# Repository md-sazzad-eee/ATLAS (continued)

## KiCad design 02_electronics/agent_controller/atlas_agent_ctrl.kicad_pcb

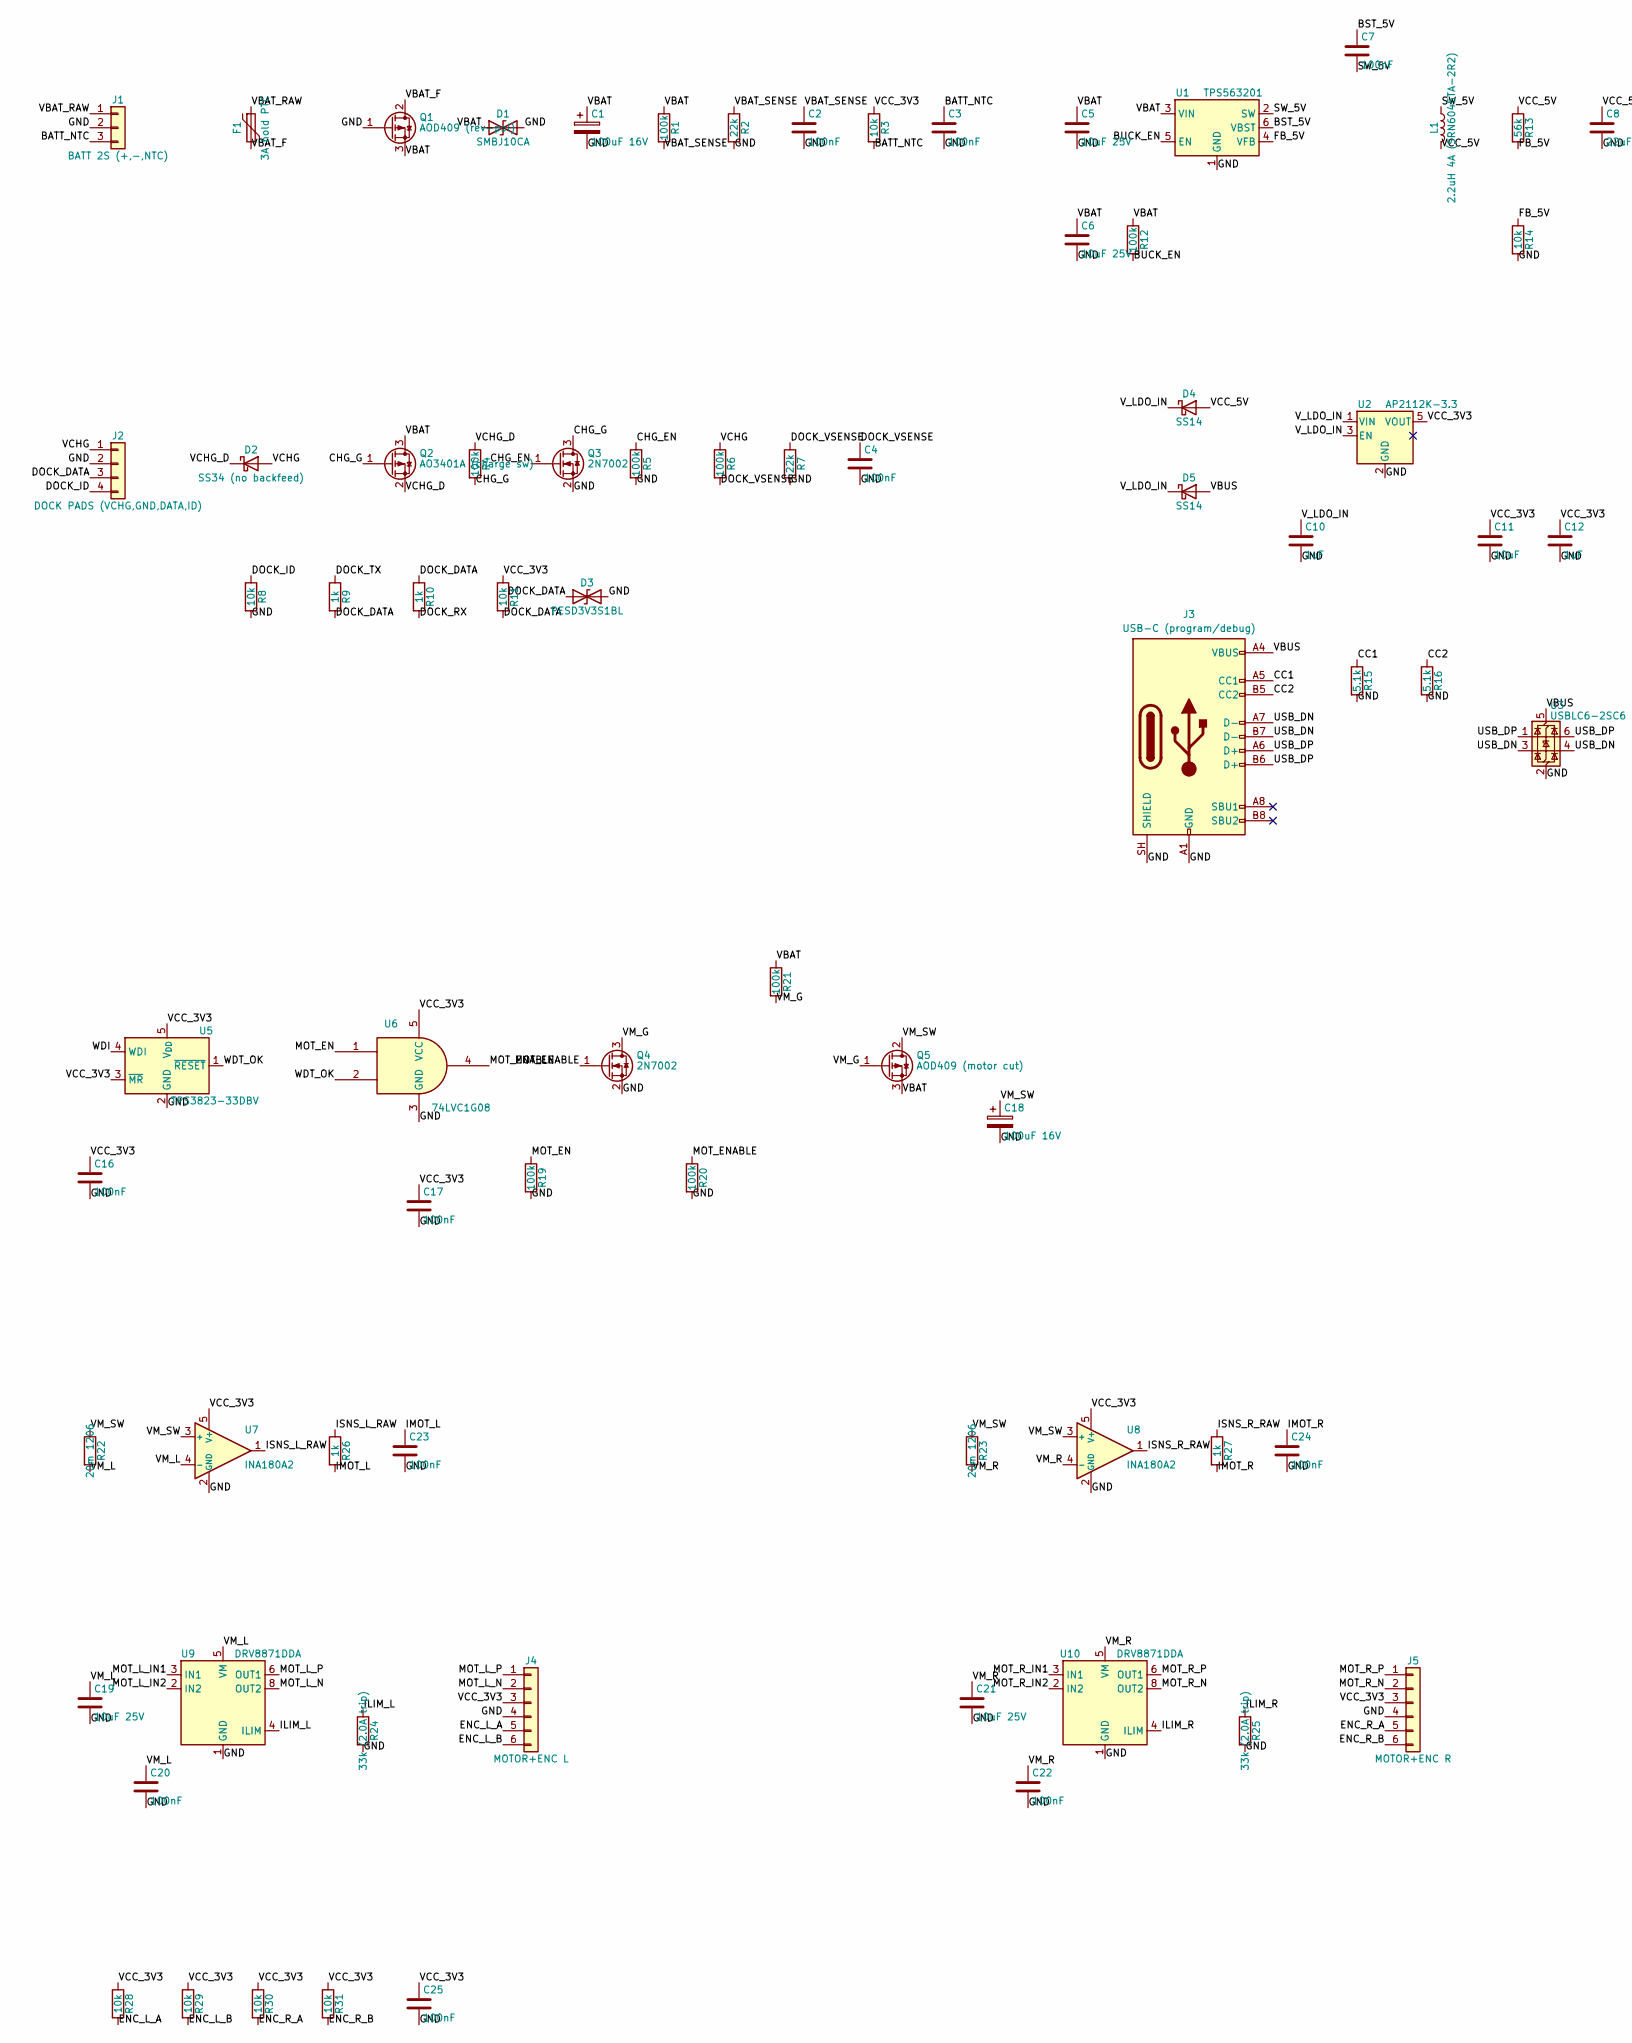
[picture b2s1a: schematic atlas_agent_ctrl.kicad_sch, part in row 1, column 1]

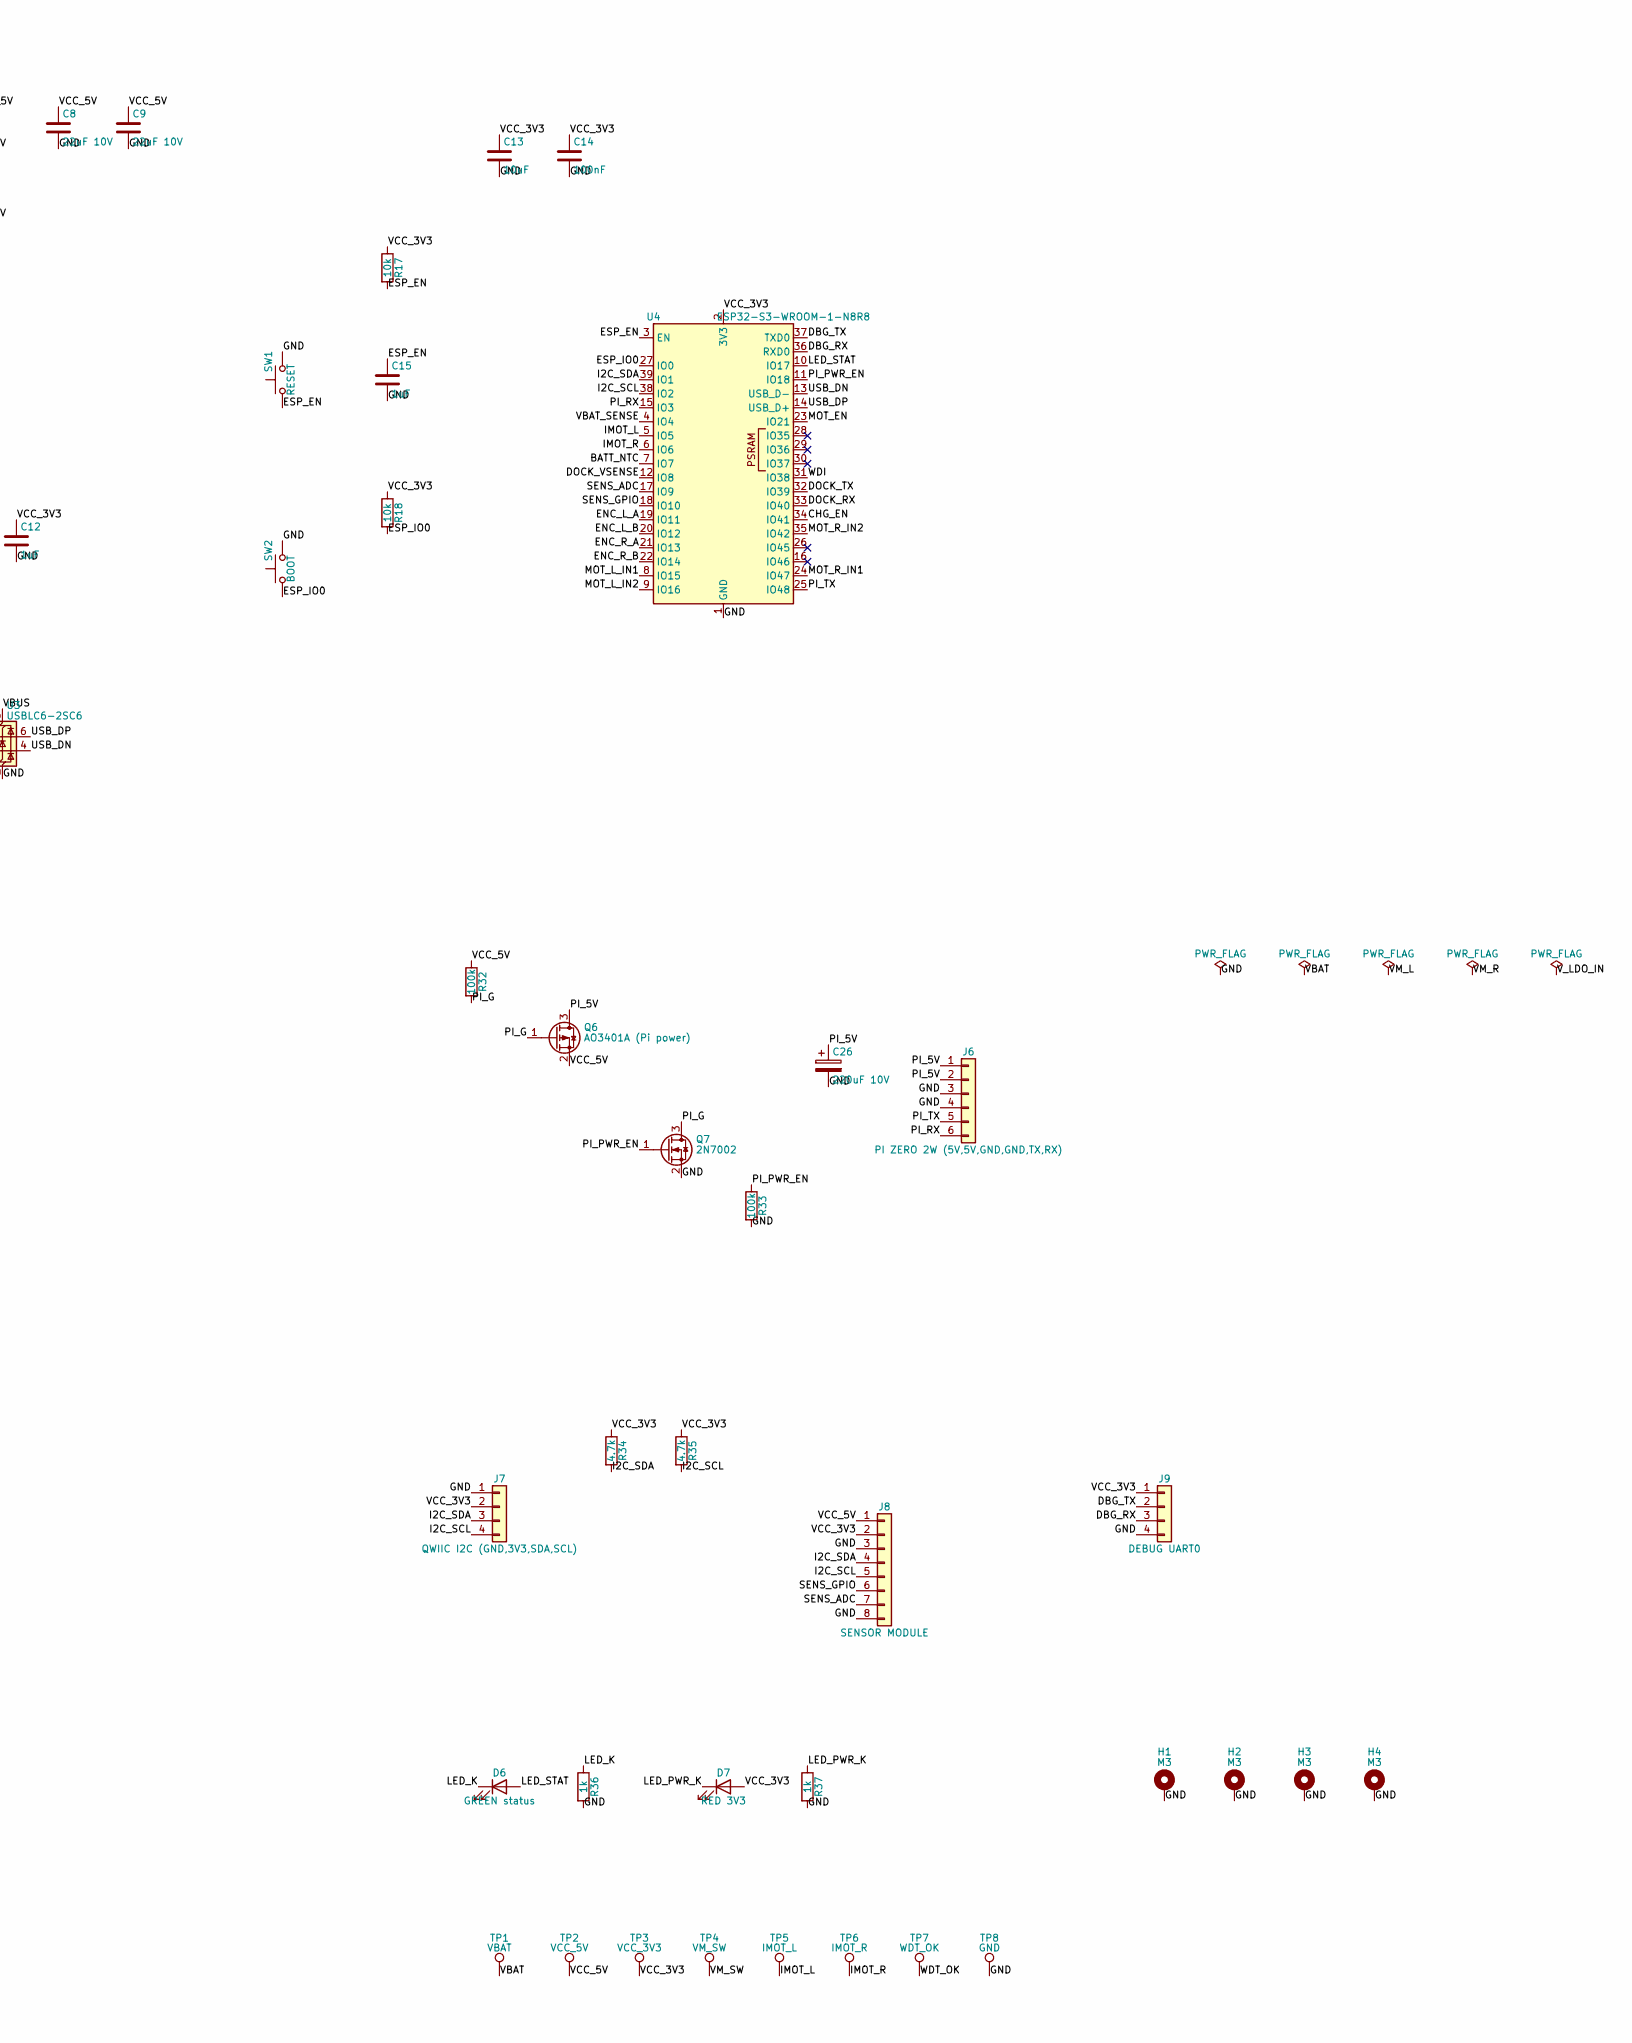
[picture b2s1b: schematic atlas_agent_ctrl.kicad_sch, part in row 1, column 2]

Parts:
C1, C18: 100uF 16V; CP_Elec_6.3x7.7
C2, C3, C4, C7, C14, C16, C17, C20, C22, C23, C24, C25: 100nF; C_0603_1608Metric
C5, C6, C19, C21: 10uF 25V; C_0805_2012Metric
C8, C9: 22uF 10V; C_0805_2012Metric
C10, C12, C15: 1uF; C_0603_1608Metric
C11, C13: 10uF; C_0805_2012Metric
C26: 220uF 10V; CP_Elec_6.3x7.7
D1: SMBJ10CA; D_SMB
D2: SS34 (no backfeed); D_SMA
D3: PESD3V3S1BL; D_SOD-323
D4, D5: SS14; D_SMA
D6: GREEN status; LED_0603_1608Metric
D7: RED 3V3; LED_0603_1608Metric
F1: 3A hold PTC; Fuse_1812_4532Metric
H1, H2, H3, H4: M3; MountingHole_3.2mm_M3_Pad_Via
J1: BATT 2S (+,-,NTC); JST_XH_B3B-XH-A_1x03_P2.50mm_Vertical
J2: DOCK PADS (VCHG,GND,DATA,ID); JST_XH_B4B-XH-A_1x04_P2.50mm_Vertical
J3: USB-C (program/debug); USB_C_Receptacle_GCT_USB4105-xx-A_16P_TopMnt_Horizontal
J4: MOTOR+ENC L; JST_PH_B6B-PH-K_1x06_P2.00mm_Vertical
J5: MOTOR+ENC R; JST_PH_B6B-PH-K_1x06_P2.00mm_Vertical
J6: PI ZERO 2W (5V,5V,GND,GND,TX,RX); JST_GH_SM06B-GHS-TB_1x06-1MP_P1.25mm_Horizontal
J7: QWIIC I2C (GND,3V3,SDA,SCL); JST_SH_SM04B-SRSS-TB_1x04-1MP_P1.00mm_Horizontal
J8: SENSOR MODULE; JST_GH_SM08B-GHS-TB_1x08-1MP_P1.25mm_Horizontal
J9: DEBUG UART0; PinHeader_1x04_P2.54mm_Vertical
L1: 2.2uH 4A (SRN6045TA-2R2); L_Bourns_SRN6045TA
Q1: AOD409 (rev-pol); TO-252-2
Q2: AO3401A (charge sw); SOT-23
Q3, Q4, Q7: 2N7002; SOT-23
Q5: AOD409 (motor cut); TO-252-2
Q6: AO3401A (Pi power); SOT-23
R1, R4, R5, R6, R12, R19, R20, R21, R32, R33: 100k; R_0603_1608Metric
R2, R7: 22k; R_0603_1608Metric
R3, R8, R11, R14, R17, R18, R28, R29, R30, R31: 10k; R_0603_1608Metric
R9, R10, R26, R27, R36, R37: 1k; R_0603_1608Metric
R13: 56k; R_0603_1608Metric
R15, R16: 5.1k; R_0603_1608Metric
R22, R23: 20m 1206; R_1206_3216Metric
R24, R25: 33k (2.0A trip); R_0603_1608Metric
R34, R35: 4.7k; R_0603_1608Metric
SW1: RESET; SW_SPST_TL3342
SW2: BOOT; SW_SPST_TL3342
TP1: VBAT; TestPoint_Pad_D1.5mm
TP2: VCC_5V; TestPoint_Pad_D1.5mm
TP3: VCC_3V3; TestPoint_Pad_D1.5mm
TP4: VM_SW; TestPoint_Pad_D1.5mm
TP5: IMOT_L; TestPoint_Pad_D1.5mm
TP6: IMOT_R; TestPoint_Pad_D1.5mm
TP7: WDT_OK; TestPoint_Pad_D1.5mm
TP8: GND; TestPoint_Pad_D1.5mm
U1: TPS563201; SOT-23-6
U2: AP2112K-3.3; SOT-23-5
U3: USBLC6-2SC6; SOT-23-6
U4: ESP32-S3-WROOM-1-N8R8; ESP32-S3-WROOM-1
U5: TPS3823-33DBV; SOT-23-5
U6: 74LVC1G08; SOT-23-5
U7, U8: INA180A2; SOT-23-5
U9, U10: DRV8871DDA; Texas_HTSOP-8-1EP_3.9x4.9mm_P1.27mm_EP2.95x4.9mm_Mask2.4x3.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

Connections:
/BATT_NTC: C3.1, J1.3, R3.2, U4.7 (IO7)
/BST_5V: C7.1, U1.6 (VBST)
/BUCK_EN: R12.2, U1.5 (EN)
/CC1: J3.A5 (CC1), R15.1
/CC2: J3.B5 (CC2), R16.1
/CHG_EN: Q3.1 (G), R5.1, U4.34 (IO41)
/CHG_G: Q2.1 (G), Q3.3 (D), R4.2
/DBG_RX: J9.3, U4.36 (RXD0)
/DBG_TX: J9.2, U4.37 (TXD0)
/DOCK_DATA: D3.1 (A1), J2.3, R9.2, R10.1, R11.2
/DOCK_ID: J2.4, R8.1
/DOCK_RX: R10.2, U4.33 (IO40)
/DOCK_TX: R9.1, U4.32 (IO39)
/DOCK_VSENSE: C4.1, R6.2, R7.1, U4.12 (IO8)
/ENC_L_A: J4.5, R28.2, U4.19 (IO11)
/ENC_L_B: J4.6, R29.2, U4.20 (IO12)
/ENC_R_A: J5.5, R30.2, U4.21 (IO13)
/ENC_R_B: J5.6, R31.2, U4.22 (IO14)
/ESP_EN: C15.1, R17.2, SW1.1, U4.3 (EN)
/ESP_IO0: R18.2, SW2.1, U4.27 (IO0)
/FB_5V: R13.2, R14.1, U1.4 (VFB)
/GND: C1.2, C2.2, C3.2, C4.2, C5.2, C6.2, C8.2, C9.2, C10.2, C11.2, C12.2, C13.2, C14.2, C15.2, C16.2, C17.2, C18.2, C19.2, C20.2, C21.2, C22.2, C23.2, C24.2, C25.2, C26.2, D1.2 (A2), D3.2 (A2), H1.1, H2.1, H3.1, H4.1, J1.2, J2.2, J3.A1 (GND), J3.A12 (GND), J3.B1 (GND), J3.B12 (GND), J3.SH (SHIELD), J4.4, J5.4, J6.3, J6.4, J7.1, J8.3, J8.8, J9.4, Q1.1 (G), Q3.2 (S), Q4.2 (S), Q7.2 (S), R2.2, R5.2, R7.2, R8.2, R14.2, R15.2, R16.2, R19.2, R20.2, R24.2, R25.2, R33.2, R36.2, R37.2, SW1.2, SW2.2, TP8.1, U1.1 (GND), U2.2 (GND), U3.2 (GND), U4.1 (GND), U4.40 (GND), U4.41 (GND), U5.2 (GND), U6.3 (GND), U7.2 (GND), U8.2 (GND), U9.1 (GND), U9.7 (GND), U9.9 (GND), U10.1 (GND), U10.7 (GND), U10.9 (GND)
/I2C_SCL: J7.4, J8.5, R35.2, U4.38 (IO2)
/I2C_SDA: J7.3, J8.4, R34.2, U4.39 (IO1)
/ILIM_L: R24.1, U9.4 (ILIM)
/ILIM_R: R25.1, U10.4 (ILIM)
/IMOT_L: C23.1, R26.2, TP5.1, U4.5 (IO5)
/IMOT_R: C24.1, R27.2, TP6.1, U4.6 (IO6)
/ISNS_L_RAW: R26.1, U7.1
/ISNS_R_RAW: R27.1, U8.1
/LED_K: D6.1 (K), R36.1
/LED_PWR_K: D7.1 (K), R37.1
/LED_STAT: D6.2 (A), U4.10 (IO17)
/MOT_EN: R19.1, U4.23 (IO21), U6.1
/MOT_ENABLE: Q4.1 (G), R20.1, U6.4
/MOT_L_IN1: U4.8 (IO15), U9.3 (IN1)
/MOT_L_IN2: U4.9 (IO16), U9.2 (IN2)
/MOT_L_N: J4.2, U9.8 (OUT2)
/MOT_L_P: J4.1, U9.6 (OUT1)
/MOT_R_IN1: U4.24 (IO47), U10.3 (IN1)
/MOT_R_IN2: U4.35 (IO42), U10.2 (IN2)
/MOT_R_N: J5.2, U10.8 (OUT2)
/MOT_R_P: J5.1, U10.6 (OUT1)
/PI_5V: C26.1, J6.1, J6.2, Q6.3 (D)
/PI_G: Q6.1 (G), Q7.3 (D), R32.2
/PI_PWR_EN: Q7.1 (G), R33.1, U4.11 (IO18)
/PI_RX: J6.6, U4.15 (IO3)
/PI_TX: J6.5, U4.25 (IO48)
/SENS_ADC: J8.7, U4.17 (IO9)
/SENS_GPIO: J8.6, U4.18 (IO10)
/SW_5V: C7.2, L1.1, U1.2 (SW)
/USB_DN: J3.A7 (D-), J3.B7 (D-), U3.3 (I/O2), U3.4 (I/O2), U4.13 (USB_D-)
/USB_DP: J3.A6 (D+), J3.B6 (D+), U3.1 (I/O1), U3.6 (I/O1), U4.14 (USB_D+)
/VBAT: C1.1, C5.1, C6.1, D1.1 (A1), Q1.3 (S), Q2.3 (D), Q5.3 (S), R1.1, R12.1, R21.1, TP1.1, U1.3 (VIN)
/VBAT_F: F1.2, Q1.2 (D)
/VBAT_RAW: F1.1, J1.1
/VBAT_SENSE: C2.1, R1.2, R2.1, U4.4 (IO4)
/VBUS: D5.2 (A), J3.A4 (VBUS), J3.A9 (VBUS), J3.B4 (VBUS), J3.B9 (VBUS), U3.5 (VBUS)
/VCC_3V3: C11.1, C12.1, C13.1, C14.1, C16.1, C17.1, C25.1, D7.2 (A), J4.3, J5.3, J7.2, J8.2, J9.1, R3.1, R11.1, R17.1, R18.1, R28.1, R29.1, R30.1, R31.1, R34.1, R35.1, TP3.1, U2.5 (VOUT), U4.2 (3V3), U5.3 (~MR), U5.5 (V_{DD}), U6.5 (VCC), U7.5 (V+), U8.5 (V+)
/VCC_5V: C8.1, C9.1, D4.2 (A), J8.1, L1.2, Q6.2 (S), R13.1, R32.1, TP2.1
/VCHG: D2.2 (A), J2.1, R6.1
/VCHG_D: D2.1 (K), Q2.2 (S), R4.1
/VM_G: Q4.3 (D), Q5.1 (G), R21.2
/VM_L: C19.1, C20.1, R22.2, U7.4 (-), U9.5 (VM)
/VM_R: C21.1, C22.1, R23.2, U8.4 (-), U10.5 (VM)
/VM_SW: C18.1, Q5.2 (D), R22.1, R23.1, TP4.1, U7.3 (+), U8.3 (+)
/V_LDO_IN: C10.1, D4.1 (K), D5.1 (K), U2.1 (VIN), U2.3 (EN)
/WDI: U4.31 (IO38), U5.4 (WDI)
/WDT_OK: TP7.1, U5.1 (~RESET), U6.2

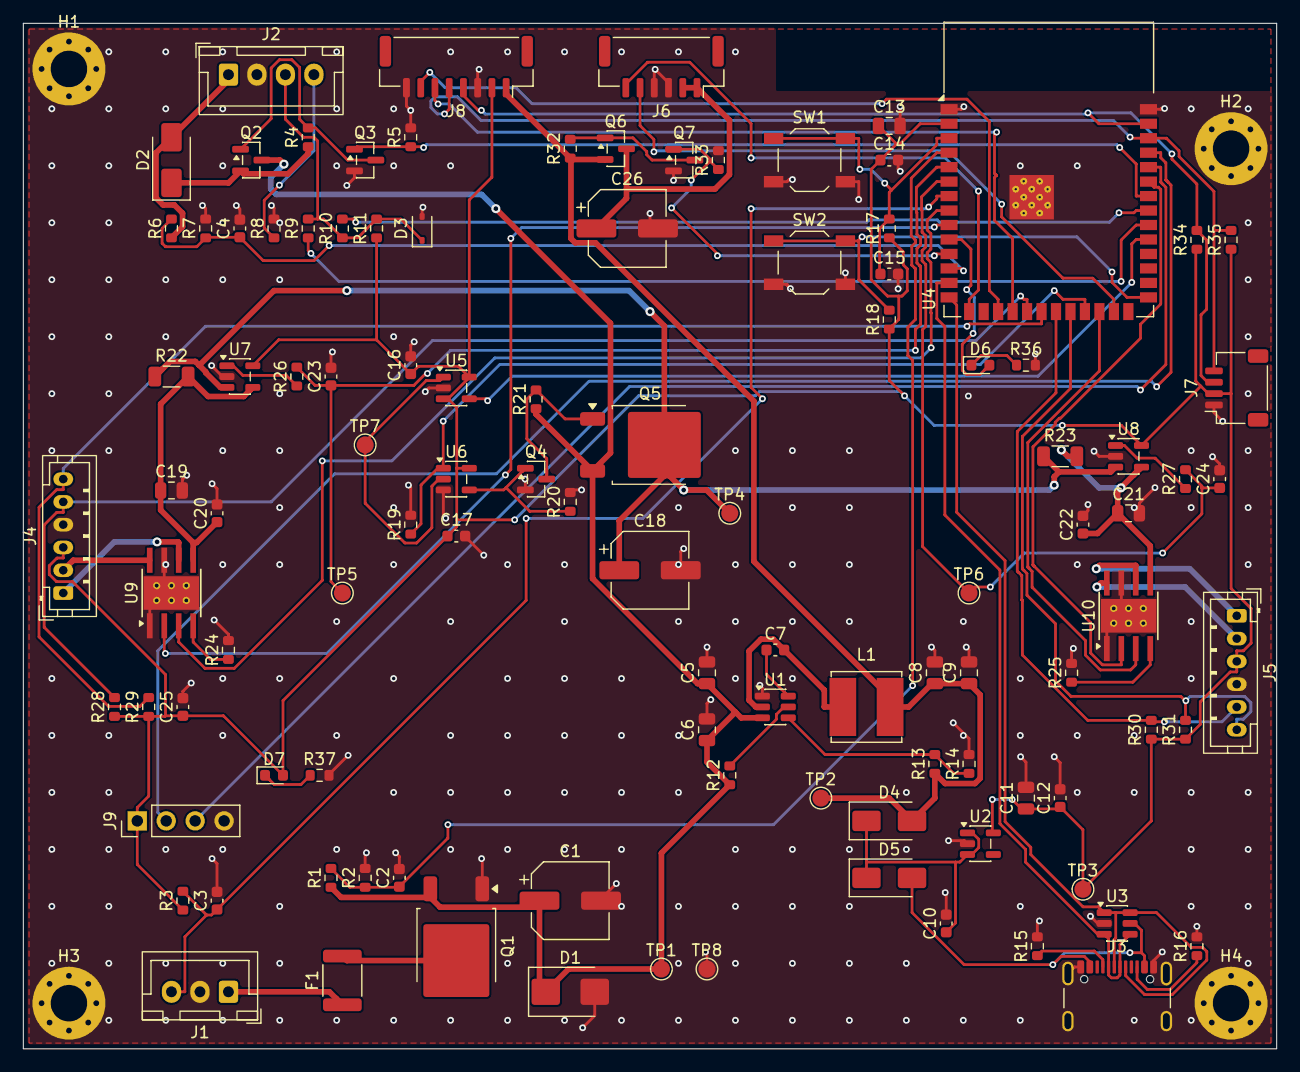
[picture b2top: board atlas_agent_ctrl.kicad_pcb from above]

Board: 2 copper layers, 110.0 x 90.0 mm, 112 parts (0 on the bottom side), 69 nets.

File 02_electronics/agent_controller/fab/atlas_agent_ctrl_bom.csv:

"Refs","Value","Footprint","Qty","DNP"
"C1","100uF 16V","Capacitor_SMD:CP_Elec_6.3x7.7","1",""
"C2","100nF","Capacitor_SMD:C_0603_1608Metric","1",""
"C3","100nF","Capacitor_SMD:C_0603_1608Metric","1",""
"C4","100nF","Capacitor_SMD:C_0603_1608Metric","1",""
"C5","10uF 25V","Capacitor_SMD:C_0805_2012Metric","1",""
"C6","10uF 25V","Capacitor_SMD:C_0805_2012Metric","1",""
"C7","100nF","Capacitor_SMD:C_0603_1608Metric","1",""
"C8","22uF 10V","Capacitor_SMD:C_0805_2012Metric","1",""
"C9","22uF 10V","Capacitor_SMD:C_0805_2012Metric","1",""
"C10","1uF","Capacitor_SMD:C_0603_1608Metric","1",""
"C11","10uF","Capacitor_SMD:C_0805_2012Metric","1",""
"C12","1uF","Capacitor_SMD:C_0603_1608Metric","1",""
"C13","10uF","Capacitor_SMD:C_0805_2012Metric","1",""
"C14","100nF","Capacitor_SMD:C_0603_1608Metric","1",""
"C15","1uF","Capacitor_SMD:C_0603_1608Metric","1",""
"C16","100nF","Capacitor_SMD:C_0603_1608Metric","1",""
"C17","100nF","Capacitor_SMD:C_0603_1608Metric","1",""
"C18","100uF 16V","Capacitor_SMD:CP_Elec_6.3x7.7","1",""
"C19","10uF 25V","Capacitor_SMD:C_0805_2012Metric","1",""
"C20","100nF","Capacitor_SMD:C_0603_1608Metric","1",""
"C21","10uF 25V","Capacitor_SMD:C_0805_2012Metric","1",""
"C22","100nF","Capacitor_SMD:C_0603_1608Metric","1",""
"C23","100nF","Capacitor_SMD:C_0603_1608Metric","1",""
"C24","100nF","Capacitor_SMD:C_0603_1608Metric","1",""
"C25","100nF","Capacitor_SMD:C_0603_1608Metric","1",""
"C26","220uF 10V","Capacitor_SMD:CP_Elec_6.3x7.7","1",""
"D1","SMBJ10CA","Diode_SMD:D_SMB","1",""
"D2","SS34 (no backfeed)","Diode_SMD:D_SMA","1",""
"D3","PESD3V3S1BL","Diode_SMD:D_SOD-323","1",""
"D4","SS14","Diode_SMD:D_SMA","1",""
"D5","SS14","Diode_SMD:D_SMA","1",""
"D6","GREEN status","LED_SMD:LED_0603_1608Metric","1",""
"D7","RED 3V3","LED_SMD:LED_0603_1608Metric","1",""
"F1","3A hold PTC","Fuse:Fuse_1812_4532Metric","1",""
"H1","M3","MountingHole:MountingHole_3.2mm_M3_Pad_Via","1",""
"H2","M3","MountingHole:MountingHole_3.2mm_M3_Pad_Via","1",""
"H3","M3","MountingHole:MountingHole_3.2mm_M3_Pad_Via","1",""
"H4","M3","MountingHole:MountingHole_3.2mm_M3_Pad_Via","1",""
"J1","BATT 2S (+,-,NTC)","Connector_JST:JST_XH_B3B-XH-A_1x03_P2.50mm_Vertical","1",""
"J2","DOCK PADS (VCHG,GND,DATA,ID)","Connector_JST:JST_XH_B4B-XH-A_1x04_P2.50mm_Vertical","1",""
"J3","USB-C (program/debug)","Connector_USB:USB_C_Receptacle_GCT_USB4105-xx-A_16P_TopMnt_Horizontal","1",""
"J4","MOTOR+ENC L","Connector_JST:JST_PH_B6B-PH-K_1x06_P2.00mm_Vertical","1",""
"J5","MOTOR+ENC R","Connector_JST:JST_PH_B6B-PH-K_1x06_P2.00mm_Vertical","1",""
"J6","PI ZERO 2W (5V,5V,GND,GND,TX,RX)","Connector_JST:JST_GH_SM06B-GHS-TB_1x06-1MP_P1.25mm_Horizontal","1",""
"J7","QWIIC I2C (GND,3V3,SDA,SCL)","Connector_JST:JST_SH_SM04B-SRSS-TB_1x04-1MP_P1.00mm_Horizontal","1",""
"J8","SENSOR MODULE","Connector_JST:JST_GH_SM08B-GHS-TB_1x08-1MP_P1.25mm_Horizontal","1",""
"J9","DEBUG UART0","Connector_PinHeader_2.54mm:PinHeader_1x04_P2.54mm_Vertical","1",""
"L1","2.2uH 4A (SRN6045TA-2R2)","Inductor_SMD:L_Bourns_SRN6045TA","1",""
"Q1","AOD409 (rev-pol)","Package_TO_SOT_SMD:TO-252-2","1",""
"Q2","AO3401A (charge sw)","Package_TO_SOT_SMD:SOT-23","1",""
"Q3","2N7002","Package_TO_SOT_SMD:SOT-23","1",""
"Q4","2N7002","Package_TO_SOT_SMD:SOT-23","1",""
"Q5","AOD409 (motor cut)","Package_TO_SOT_SMD:TO-252-2","1",""
"Q6","AO3401A (Pi power)","Package_TO_SOT_SMD:SOT-23","1",""
"Q7","2N7002","Package_TO_SOT_SMD:SOT-23","1",""
"R1","100k","Resistor_SMD:R_0603_1608Metric","1",""
"R2","22k","Resistor_SMD:R_0603_1608Metric","1",""
"R3","10k","Resistor_SMD:R_0603_1608Metric","1",""
"R4","100k","Resistor_SMD:R_0603_1608Metric","1",""
"R5","100k","Resistor_SMD:R_0603_1608Metric","1",""
"R6","100k","Resistor_SMD:R_0603_1608Metric","1",""
"R7","22k","Resistor_SMD:R_0603_1608Metric","1",""
"R8","10k","Resistor_SMD:R_0603_1608Metric","1",""
"R9","1k","Resistor_SMD:R_0603_1608Metric","1",""
"R10","1k","Resistor_SMD:R_0603_1608Metric","1",""
"R11","10k","Resistor_SMD:R_0603_1608Metric","1",""
"R12","100k","Resistor_SMD:R_0603_1608Metric","1",""
"R13","56k","Resistor_SMD:R_0603_1608Metric","1",""
"R14","10k","Resistor_SMD:R_0603_1608Metric","1",""
"R15","5.1k","Resistor_SMD:R_0603_1608Metric","1",""
"R16","5.1k","Resistor_SMD:R_0603_1608Metric","1",""
"R17","10k","Resistor_SMD:R_0603_1608Metric","1",""
"R18","10k","Resistor_SMD:R_0603_1608Metric","1",""
"R19","100k","Resistor_SMD:R_0603_1608Metric","1",""
"R20","100k","Resistor_SMD:R_0603_1608Metric","1",""
"R21","100k","Resistor_SMD:R_0603_1608Metric","1",""
"R22","20m 1206","Resistor_SMD:R_1206_3216Metric","1",""
"R23","20m 1206","Resistor_SMD:R_1206_3216Metric","1",""
"R24","33k (2.0A trip)","Resistor_SMD:R_0603_1608Metric","1",""
"R25","33k (2.0A trip)","Resistor_SMD:R_0603_1608Metric","1",""
"R26","1k","Resistor_SMD:R_0603_1608Metric","1",""
"R27","1k","Resistor_SMD:R_0603_1608Metric","1",""
"R28","10k","Resistor_SMD:R_0603_1608Metric","1",""
"R29","10k","Resistor_SMD:R_0603_1608Metric","1",""
"R30","10k","Resistor_SMD:R_0603_1608Metric","1",""
"R31","10k","Resistor_SMD:R_0603_1608Metric","1",""
"R32","100k","Resistor_SMD:R_0603_1608Metric","1",""
"R33","100k","Resistor_SMD:R_0603_1608Metric","1",""
"R34","4.7k","Resistor_SMD:R_0603_1608Metric","1",""
"R35","4.7k","Resistor_SMD:R_0603_1608Metric","1",""
"R36","1k","Resistor_SMD:R_0603_1608Metric","1",""
"R37","1k","Resistor_SMD:R_0603_1608Metric","1",""
"SW1","RESET","Button_Switch_SMD:SW_SPST_TL3342","1",""
"SW2","BOOT","Button_Switch_SMD:SW_SPST_TL3342","1",""
"TP1","VBAT","TestPoint:TestPoint_Pad_D1.5mm","1",""
"TP2","VCC_5V","TestPoint:TestPoint_Pad_D1.5mm","1",""
"TP3","VCC_3V3","TestPoint:TestPoint_Pad_D1.5mm","1",""
"TP4","VM_SW","TestPoint:TestPoint_Pad_D1.5mm","1",""
"TP5","IMOT_L","TestPoint:TestPoint_Pad_D1.5mm","1",""
"TP6","IMOT_R","TestPoint:TestPoint_Pad_D1.5mm","1",""
"TP7","WDT_OK","TestPoint:TestPoint_Pad_D1.5mm","1",""
"TP8","GND","TestPoint:TestPoint_Pad_D1.5mm","1",""
"U1","TPS563201","Package_TO_SOT_SMD:SOT-23-6","1",""
"U2","AP2112K-3.3","Package_TO_SOT_SMD:SOT-23-5","1",""
"U3","USBLC6-2SC6","Package_TO_SOT_SMD:SOT-23-6","1",""
"U4","ESP32-S3-WROOM-1-N8R8","RF_Module:ESP32-S3-WROOM-1","1",""
"U5","TPS3823-33DBV","Package_TO_SOT_SMD:SOT-23-5","1",""
"U6","74LVC1G08","Package_TO_SOT_SMD:SOT-23-5","1",""
"U7","INA180A2","Package_TO_SOT_SMD:SOT-23-5","1",""
"U8","INA180A2","Package_TO_SOT_SMD:SOT-23-5","1",""
"U9","DRV8871DDA","Package_SO:Texas_HTSOP-8-1EP_3.9x4.9mm_P1.27mm_EP2.95x4.9mm_Mask2.4x3.1mm_ThermalVias","1",""
"U10","DRV8871DDA","Package_SO:Texas_HTSOP-8-1EP_3.9x4.9mm_P1.27mm_EP2.95x4.9mm_Mask2.4x3.1mm_ThermalVias","1",""

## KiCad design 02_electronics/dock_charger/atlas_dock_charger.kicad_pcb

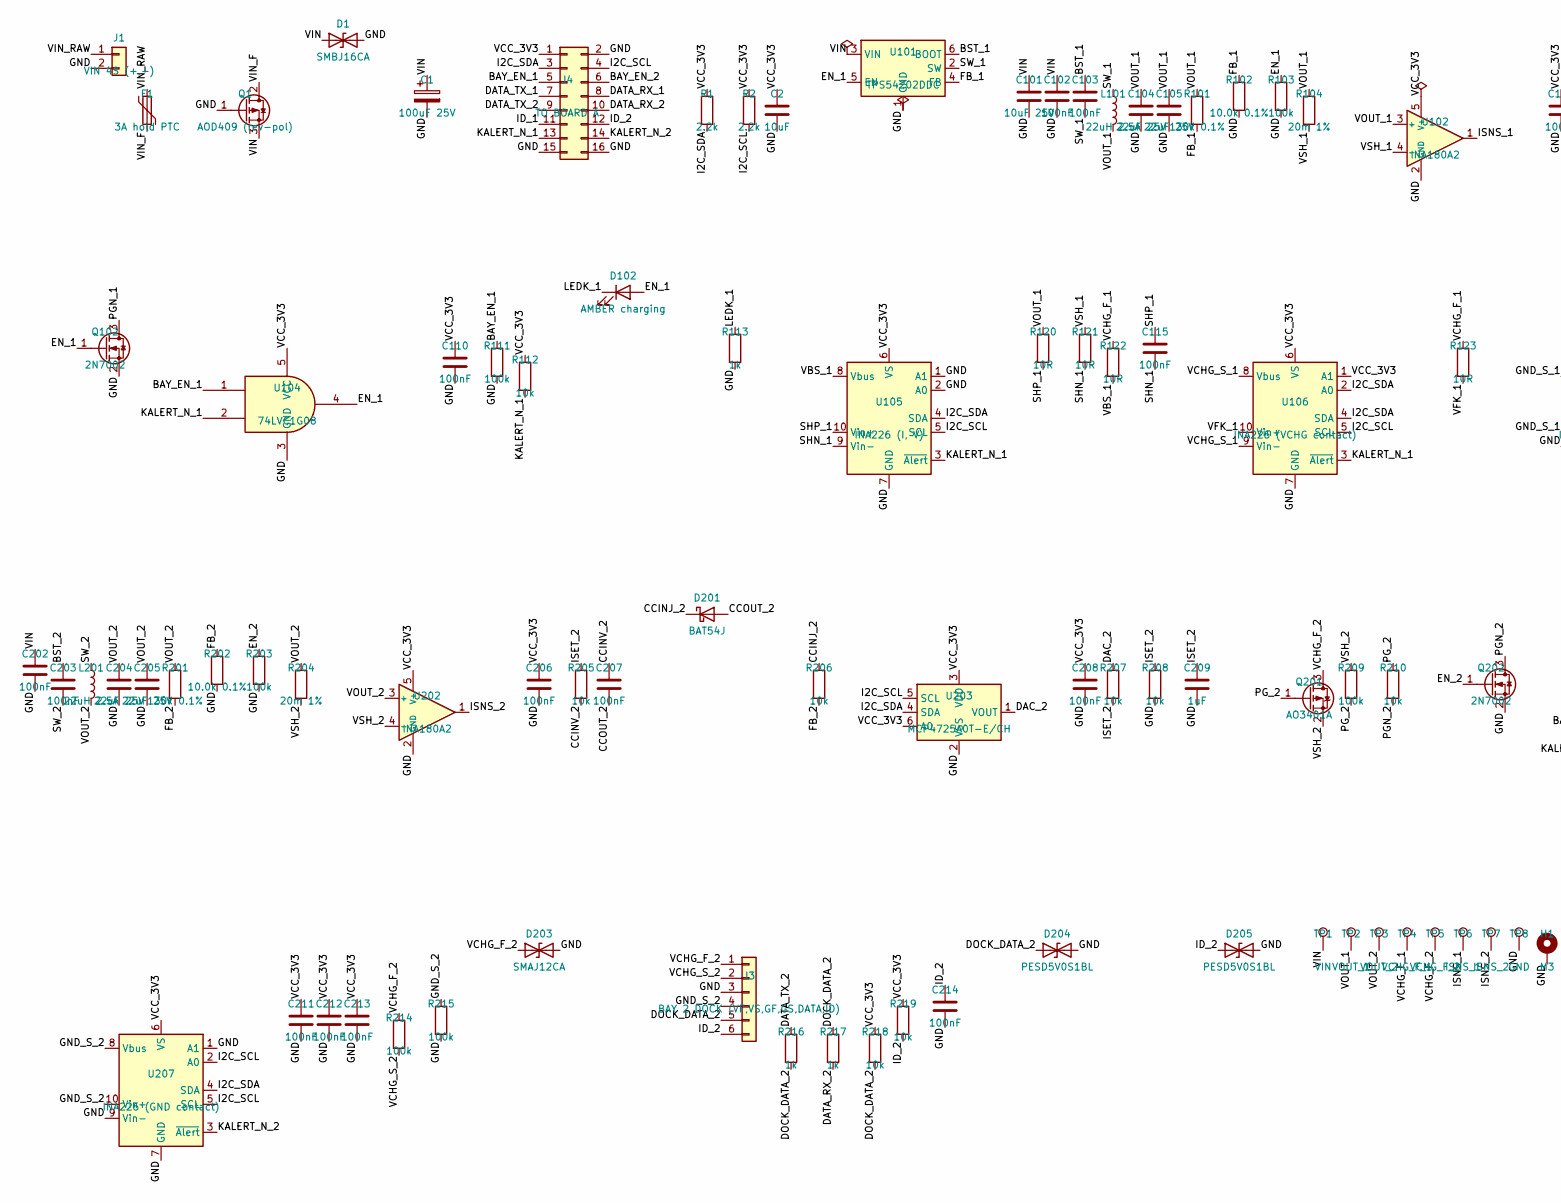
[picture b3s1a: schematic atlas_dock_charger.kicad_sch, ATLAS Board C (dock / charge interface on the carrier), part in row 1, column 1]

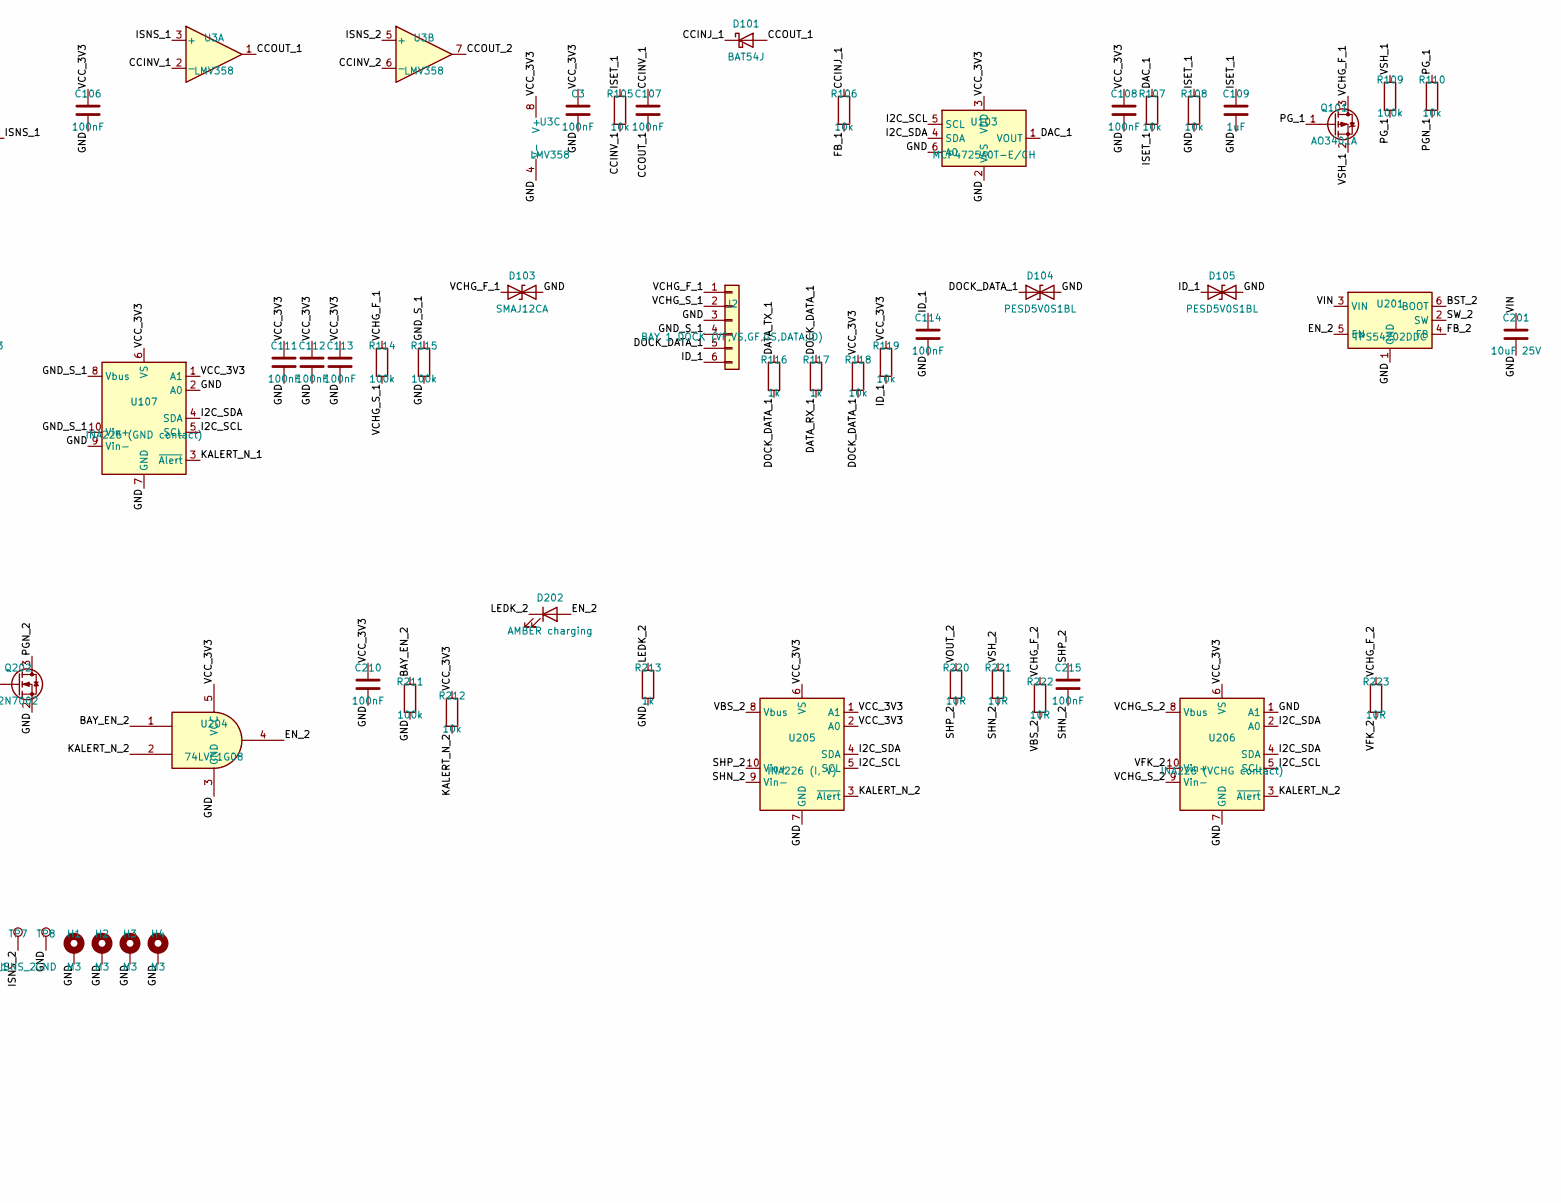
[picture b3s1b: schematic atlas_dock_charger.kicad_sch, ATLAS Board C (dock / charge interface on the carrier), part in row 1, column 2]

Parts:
C1: 100uF 25V; CP_Elec_8x10
C2: 10uF; C_0805_2012Metric
C3, C102, C103, C106, C107, C108, C110, C111, C112, C113, C114, C115, C202, C203, C206, C207, C208, C210, C211, C212, C213, C214, C215: 100nF; C_0603_1608Metric
C101, C201: 10uF 25V; C_1206_3216Metric
C104, C105, C204, C205: 22uF 25V; C_1206_3216Metric
C109, C209: 1uF; C_0603_1608Metric
D1: SMBJ16CA; D_SMB
D101, D201: BAT54J; D_SOD-323
D102, D202: AMBER charging; LED_0603_1608Metric
D103, D203: SMAJ12CA; D_SMA
D104, D105, D204, D205: PESD5V0S1BL; D_SOD-323
F1: 3A hold PTC; Fuse_1812_4532Metric
H1, H2, H3, H4: M3; MountingHole_3.2mm_M3_Pad_Via
J1: VIN 4S (+,-); AMASS_XT30PW-M_1x02_P2.50mm_Horizontal
J2: BAY 1 DOCK (VF,VS,GF,GS,DATA,ID); JST_XH_B6B-XH-A_1x06_P2.50mm_Vertical
J3: BAY 2 DOCK (VF,VS,GF,GS,DATA,ID); JST_XH_B6B-XH-A_1x06_P2.50mm_Vertical
J4: TO BOARD A; PinHeader_2x08_P2.54mm_Vertical
L101, L201: 22uH 2.5A; L_Bourns_SRR1260
Q1: AOD409 (rev-pol); TO-252-2
Q101, Q201: AO3401A; SOT-23
Q102, Q202: 2N7002; SOT-23
R1, R2: 2.2k; R_0603_1608Metric
R101, R201: 130k 0.1%; R_0603_1608Metric
R102, R202: 10.0k 0.1%; R_0603_1608Metric
R103, R109, R111, R114, R115, R203, R209, R211, R214, R215: 100k; R_0603_1608Metric
R104, R204: 20m 1%; R_1206_3216Metric
R105, R106, R107, R108, R110, R112, R118, R119, R205, R206, R207, R208, R210, R212, R218, R219: 10k; R_0603_1608Metric
R113, R116, R117, R213, R216, R217: 1k; R_0603_1608Metric
R120, R121, R122, R123, R220, R221, R222, R223: 10R; R_0603_1608Metric
TP1: VIN; TestPoint_Pad_D1.5mm
TP2: VOUT_1; TestPoint_Pad_D1.5mm
TP3: VOUT_2; TestPoint_Pad_D1.5mm
TP4: VCHG_F_1; TestPoint_Pad_D1.5mm
TP5: VCHG_F_2; TestPoint_Pad_D1.5mm
TP6: ISNS_1; TestPoint_Pad_D1.5mm
TP7: ISNS_2; TestPoint_Pad_D1.5mm
TP8: GND; TestPoint_Pad_D1.5mm
U3: LMV358; SOIC-8_3.9x4.9mm_P1.27mm
U101, U201: TPS54202DDC; SOT-23-6
U102, U202: INA180A2; SOT-23-5
U103, U203: MCP4725A0T-E/CH; SOT-23-6
U104, U204: 74LVC1G08; SOT-23-5
U105, U205: INA226 (I, V); MSOP-10_3x3mm_P0.5mm
U106, U206: INA226 (VCHG contact); MSOP-10_3x3mm_P0.5mm
U107, U207: INA226 (GND contact); MSOP-10_3x3mm_P0.5mm

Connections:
/BAY_EN_1: J4.5, R111.1, U104.1
/BAY_EN_2: J4.6, R211.1, U204.1
/BST_1: C103.1, U101.6 (BOOT)
/BST_2: C203.1, U201.6 (BOOT)
/CCINJ_1: D101.1 (K), R106.1
/CCINJ_2: D201.1 (K), R206.1
/CCINV_1: C107.1, R105.2, U3.2 (-)
/CCINV_2: C207.1, R205.2, U3.6 (-)
/CCOUT_1: C107.2, D101.2 (A), U3.1
/CCOUT_2: C207.2, D201.2 (A), U3.7
/DAC_1: R107.1, U103.1 (VOUT)
/DAC_2: R207.1, U203.1 (VOUT)
/DATA_RX_1: J4.8, R117.2
/DATA_RX_2: J4.10, R217.2
/DATA_TX_1: J4.7, R116.1
/DATA_TX_2: J4.9, R216.1
/DOCK_DATA_1: D104.1 (A1), J2.5, R116.2, R117.1, R118.2
/DOCK_DATA_2: D204.1 (A1), J3.5, R216.2, R217.1, R218.2
/EN_1: D102.2 (A), Q102.1 (G), R103.1, U101.5 (EN), U104.4
/EN_2: D202.2 (A), Q202.1 (G), R203.1, U201.5 (EN), U204.4
/FB_1: R101.2, R102.1, R106.2, U101.4 (FB)
/FB_2: R201.2, R202.1, R206.2, U201.4 (FB)
/GND: C1.2, C2.2, C3.2, C101.2, C102.2, C104.2, C105.2, C106.2, C108.2, C109.2, C110.2, C111.2, C112.2, C113.2, C114.2, C201.2, C202.2, C204.2, C205.2, C206.2, C208.2, C209.2, C210.2, C211.2, C212.2, C213.2, C214.2, D1.2 (A2), D103.2 (A2), D104.2 (A2), D105.2 (A2), D203.2 (A2), D204.2 (A2), D205.2 (A2), H1.1, H2.1, H3.1, H4.1, J1.2, J2.3, J3.3, J4.2, J4.15, J4.16, Q1.1 (G), Q102.2 (S), Q202.2 (S), R102.2, R103.2, R108.2, R111.2, R113.2, R115.2, R202.2, R203.2, R208.2, R211.2, R213.2, R215.2, TP8.1, U3.4 (V-), U101.1 (GND), U102.2 (GND), U103.2 (VSS), U103.6 (A0), U104.3 (GND), U105.1 (A1), U105.2 (A0), U105.7 (GND), U106.7 (GND), U107.2 (A0), U107.7 (GND), U107.9 (Vin-), U201.1 (GND), U202.2 (GND), U203.2 (VSS), U204.3 (GND), U205.7 (GND), U206.1 (A1), U206.7 (GND), U207.1 (A1), U207.7 (GND), U207.9 (Vin-)
/GND_S_1: J2.4, R115.1, U107.8 (Vbus), U107.10 (Vin+)
/GND_S_2: J3.4, R215.1, U207.8 (Vbus), U207.10 (Vin+)
/I2C_SCL: J4.4, R2.2, U103.5 (SCL), U105.5 (SCL), U106.5 (SCL), U107.5 (SCL), U203.5 (SCL), U205.5 (SCL), U206.5 (SCL), U207.2 (A0), U207.5 (SCL)
/I2C_SDA: J4.3, R1.2, U103.4 (SDA), U105.4 (SDA), U106.2 (A0), U106.4 (SDA), U107.4 (SDA), U203.4 (SDA), U205.4 (SDA), U206.2 (A0), U206.4 (SDA), U207.4 (SDA)
/ID_1: C114.1, D105.1 (A1), J2.6, J4.11, R119.2
/ID_2: C214.1, D205.1 (A1), J3.6, J4.12, R219.2
/ISET_1: C109.1, R105.1, R107.2, R108.1
/ISET_2: C209.1, R205.1, R207.2, R208.1
/ISNS_1: TP6.1, U3.3 (+), U102.1
/ISNS_2: TP7.1, U3.5 (+), U202.1
/KALERT_N_1: J4.13, R112.2, U104.2, U105.3 (~Alert), U106.3 (~Alert), U107.3 (~Alert)
/KALERT_N_2: J4.14, R212.2, U204.2, U205.3 (~Alert), U206.3 (~Alert), U207.3 (~Alert)
/LEDK_1: D102.1 (K), R113.1
/LEDK_2: D202.1 (K), R213.1
/PGN_1: Q102.3 (D), R110.2
/PGN_2: Q202.3 (D), R210.2
/PG_1: Q101.1 (G), R109.2, R110.1
/PG_2: Q201.1 (G), R209.2, R210.1
/SHN_1: C115.2, R121.2, U105.9 (Vin-)
/SHN_2: C215.2, R221.2, U205.9 (Vin-)
/SHP_1: C115.1, R120.2, U105.10 (Vin+)
/SHP_2: C215.1, R220.2, U205.10 (Vin+)
/SW_1: C103.2, L101.1, U101.2 (SW)
/SW_2: C203.2, L201.1, U201.2 (SW)
/VBS_1: R122.2, U105.8 (Vbus)
/VBS_2: R222.2, U205.8 (Vbus)
/VCC_3V3: C2.1, C3.1, C106.1, C108.1, C110.1, C111.1, C112.1, C113.1, C206.1, C208.1, C210.1, C211.1, C212.1, C213.1, J4.1, R1.1, R2.1, R112.1, R118.1, R119.1, R212.1, R218.1, R219.1, U3.8 (V+), U102.5 (V+), U103.3 (VDD), U104.5 (VCC), U105.6 (VS), U106.1 (A1), U106.6 (VS), U107.1 (A1), U107.6 (VS), U202.5 (V+), U203.3 (VDD), U203.6 (A0), U204.5 (VCC), U205.1 (A1), U205.2 (A0), U205.6 (VS), U206.6 (VS), U207.6 (VS)
/VCHG_F_1: D103.1 (A1), J2.1, Q101.3 (D), R114.1, R122.1, R123.1, TP4.1
/VCHG_F_2: D203.1 (A1), J3.1, Q201.3 (D), R214.1, R222.1, R223.1, TP5.1
/VCHG_S_1: J2.2, R114.2, U106.8 (Vbus), U106.9 (Vin-)
/VCHG_S_2: J3.2, R214.2, U206.8 (Vbus), U206.9 (Vin-)
/VFK_1: R123.2, U106.10 (Vin+)
/VFK_2: R223.2, U206.10 (Vin+)
/VIN: C1.1, C101.1, C102.1, C201.1, C202.1, D1.1 (A1), Q1.3 (S), TP1.1, U101.3 (VIN), U201.3 (VIN)
/VIN_F: F1.2, Q1.2 (D)
/VIN_RAW: F1.1, J1.1
/VOUT_1: C104.1, C105.1, L101.2, R101.1, R104.1, R120.1, TP2.1, U102.3 (+)
/VOUT_2: C204.1, C205.1, L201.2, R201.1, R204.1, R220.1, TP3.1, U202.3 (+)
/VSH_1: Q101.2 (S), R104.2, R109.1, R121.1, U102.4 (-)
/VSH_2: Q201.2 (S), R204.2, R209.1, R221.1, U202.4 (-)
